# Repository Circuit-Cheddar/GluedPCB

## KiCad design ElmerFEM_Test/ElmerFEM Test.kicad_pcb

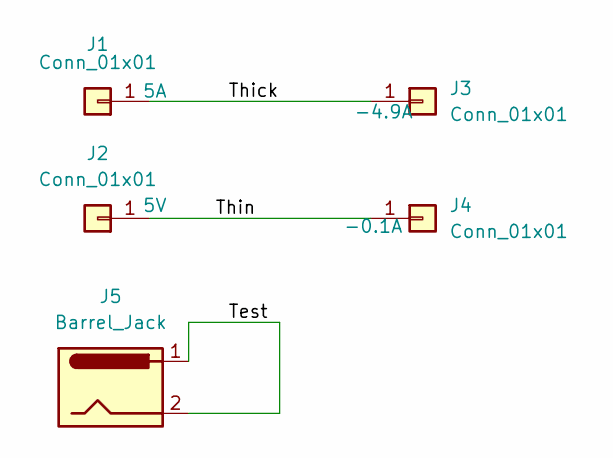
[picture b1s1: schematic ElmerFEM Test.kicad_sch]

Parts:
J1, J2, J3, J4: Conn_01x01; Banana_Jack_1Pin
J5: Barrel_Jack; BatteryHolder_Keystone_103_1x20mm

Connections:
/Test: J5.1, J5.2
/Thick: J1.1 (Pin_1_1), J3.1 (Pin_1_1)
/Thin: J2.1 (Pin_1_1), J4.1 (Pin_1_1)

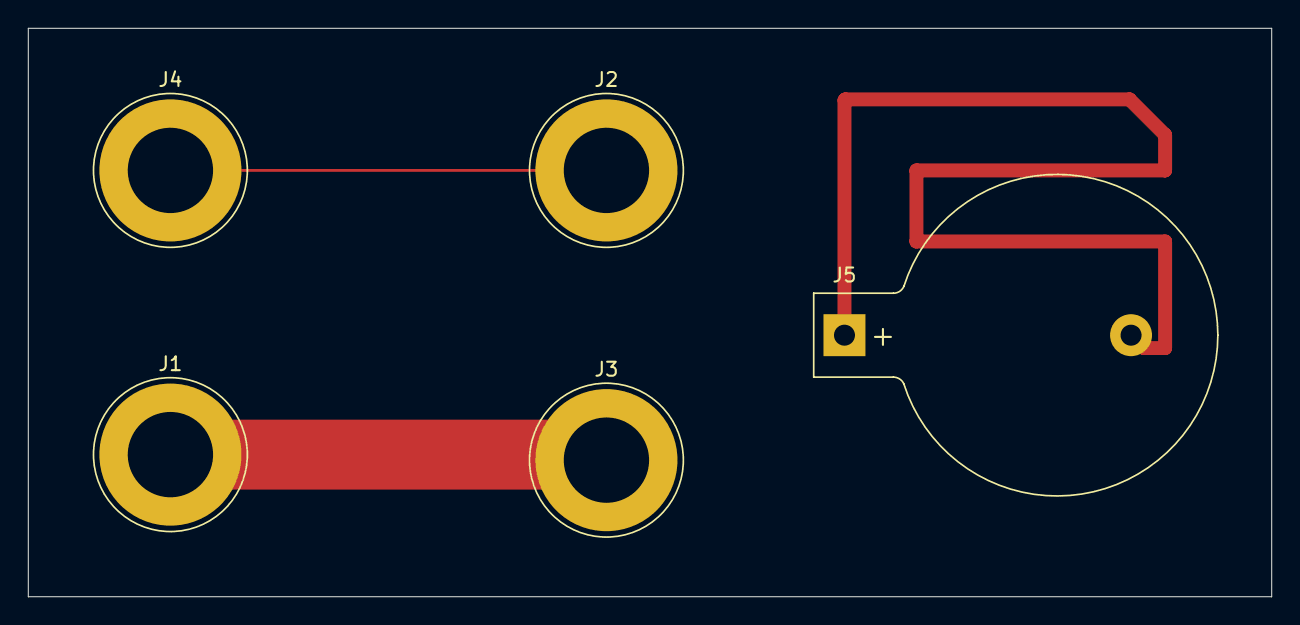
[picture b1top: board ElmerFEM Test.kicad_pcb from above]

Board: 4 copper layers, 88.9 x 40.6 mm, 5 parts (0 on the bottom side), 3 nets.
